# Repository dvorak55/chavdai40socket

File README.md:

# Chavdai40% Socket のご紹介

 - Chavdai40%は、ちゃぶだいよんじゅっぱーせんと、と読みます
 - 古き良きちゃぶ台をイメージしました

### ロゴ

### 基板写真

## ★★★　詳細な組み立て説明はキットに同梱の説明書に記載しておりますので省略しますが、この場所では写真が掲載可能なので、デコレーション例や、組み立てで難しそうな点をご紹介いたします　★★★

## Chavdai40% Socket（ソケット）の特徴
 - デコレーションできる、コンパクトで健気なキーボード
    - 40％キーボードというサイズ感（キー数44、または42）
    - ソケット対応なので、とりあえず組み立てて後でデコレーションするのも可能です
    - キーボードケースが付属しているので、持ち運びしやすいです
 - リーズナブルなキーキャップが選べます
    - Amazonでも売っているキーキャップが使えます
    - ちょっと高価なキーキャップも、もちろん使えます
    - 日本語キーボードの縦長Enterキーは使えません
 - Vial（ヴァイアル）というソフトに対応しています
    - 40％キーボードでも数字と記号が入力できます
    - Ctrl＋a等の組み合わせを1つのキーに登録することも可能です
 - USB-Cでパソコン／スマホ／タブレットと接続して使えます

## Chavdai40%の組み立て例
### 組立例１（Chavdai40% Socket ＋ ダイソー リメイクシート ナチュラルウッド ホワイト ＋ mtマスキングテープ ドットシリーズ（オレンジ、ピンク、青） ＋ mtマスキングテープ幅3ｍｍシリーズ ＋ ダイソー マスキングテープ ＋ ダイソー デコレーションシール ＋ 一般的な白地に黒文字のキーキャップ）
なるべくリーズナブルにおしゃれなデザインを目標に、ダイソーの白い木目のリメイクシートを下地に、パステル調のマスキングテープでデコレーションしてみました。キーキャップは同じくリーズナブルに入手できる白地に黒文字のキーキャップを取り付けて、シンプルながらも明るい印象に仕上げました。  

マスキングテープをランダムに配置して、おしゃれな感じにしてみました。  

リメイクシートとキーキャップセットは以下で購入可能です（2026年8月15日現在）  

●リメイクシート（ダイソー）  
[https://jp.daisonet.com/products/4900662759840)](https://jp.daisonet.com/products/4900662759840)  
●マスキングテープ（mtドット系）  
[https://shop.masking-tape.jp/products/list.php?category=99](https://shop.masking-tape.jp/products/list.php?category=99)  
●キーキャップ（Amazon.co.jp）  
[https://amzn.asia/d/0fVIauQW](https://amzn.asia/d/0fVIauQW)  

### 組立例２（Chavdai40% ＋ mtリメイクシートKapitza SUN ＋ Tai-Hao ABS Cubic Miami Surf）
※こちらはChavdai40％の以前のモデルでのデコレーション事例です。  
赤色の丸がかわいいリメイクシートと、ピンク色のキーキャップを組み合わせると、とってもポップな色合いになります。  

アクセントカラーの青色キーキャップが華を添えている感じですね。  

リメイクシートとキーキャップセットは現在は入手できません。  

### 組立例３（Chavdai40% ＋ mtリメイクシートKapitza FUJI ＋ GMK ECLIPSE）
※こちらはChavdai40％の以前のモデルでのデコレーション事例です。  
青色の三角がクールなリメイクシートと、青色黒色のキーキャップを組み合わせると、とっても引き締まった色合いになります。  

GMKのキーキャップセットなので、スペースキーを分割できます。この写真ではスペースキーが打ちやすいように上下逆につけています。  

リメイクシートとキーキャップセットは現在は入手できません。  

## デフォルトのキーマップ（JISの設定です）
### 44キーのキーマップ  
#### デフォルトレイヤー  

#### レイヤー1  

### 42キーのキーマップ
#### デフォルトレイヤー  

#### レイヤー1  

### 日本語キーボードか、英字キーボードかについて
Chavdai40% Socketでは、キットに付属の説明書内で、最初のキーマップは日本語キーボードのJISの設定にしています。  
もし英字キーボードの設定にしたい場合は、Vialの画面で以下の箇所を設定してください。  
上のメニューから『Keyboard Layout』を選び、その中から一番上にある『QWERTY』をクリックして選択します。  
これで、日本語キーボードのJISから、英字キーボードになります。  

## その他の問い合わせ先
X（twitter）: dombrick45 https://twitter.com/dombrick45  
※キットに同梱の説明書にメールアドレスが記載されております。

## 難しそうなポイント
### １．スタビライザーの取り付け
スタビライザーは、説明書にあるように大きな方の穴に爪を引っ掛けた後、小さい方の穴にもう片方の爪を嵌める手順で取り付けます。  
このスタビライザーを取り付けた後、キースイッチ・キーキャップを付けると、キースイッチがうまく戻らないことがあります。  
その場合は、キーキャップをつまんで、上下左右に動かしてみて下さい。 　
少し遊びができると、キースイッチがうまく戻るようになります。  
### ２．デコレーションの後に、キースイッチ・スタビライザーを取り付ける
おもて面にデコレーションのシール・シートを貼ると、キースイッチ・スタビライザーを取り付ける時、少しキツくなります。  
簡単にするため、キースイッチ・スタビライザーの取り付け箇所のシール・シートに、あらかじめ鉛筆やボールペンで穴を空けておくと良いです。
また、デコレーションを3枚ほど重ねた箇所のスイッチ取り付けはかなり辛いので、その場合は、スイッチの穴の箇所だけデコレーションを破いて取り除くと良いです。

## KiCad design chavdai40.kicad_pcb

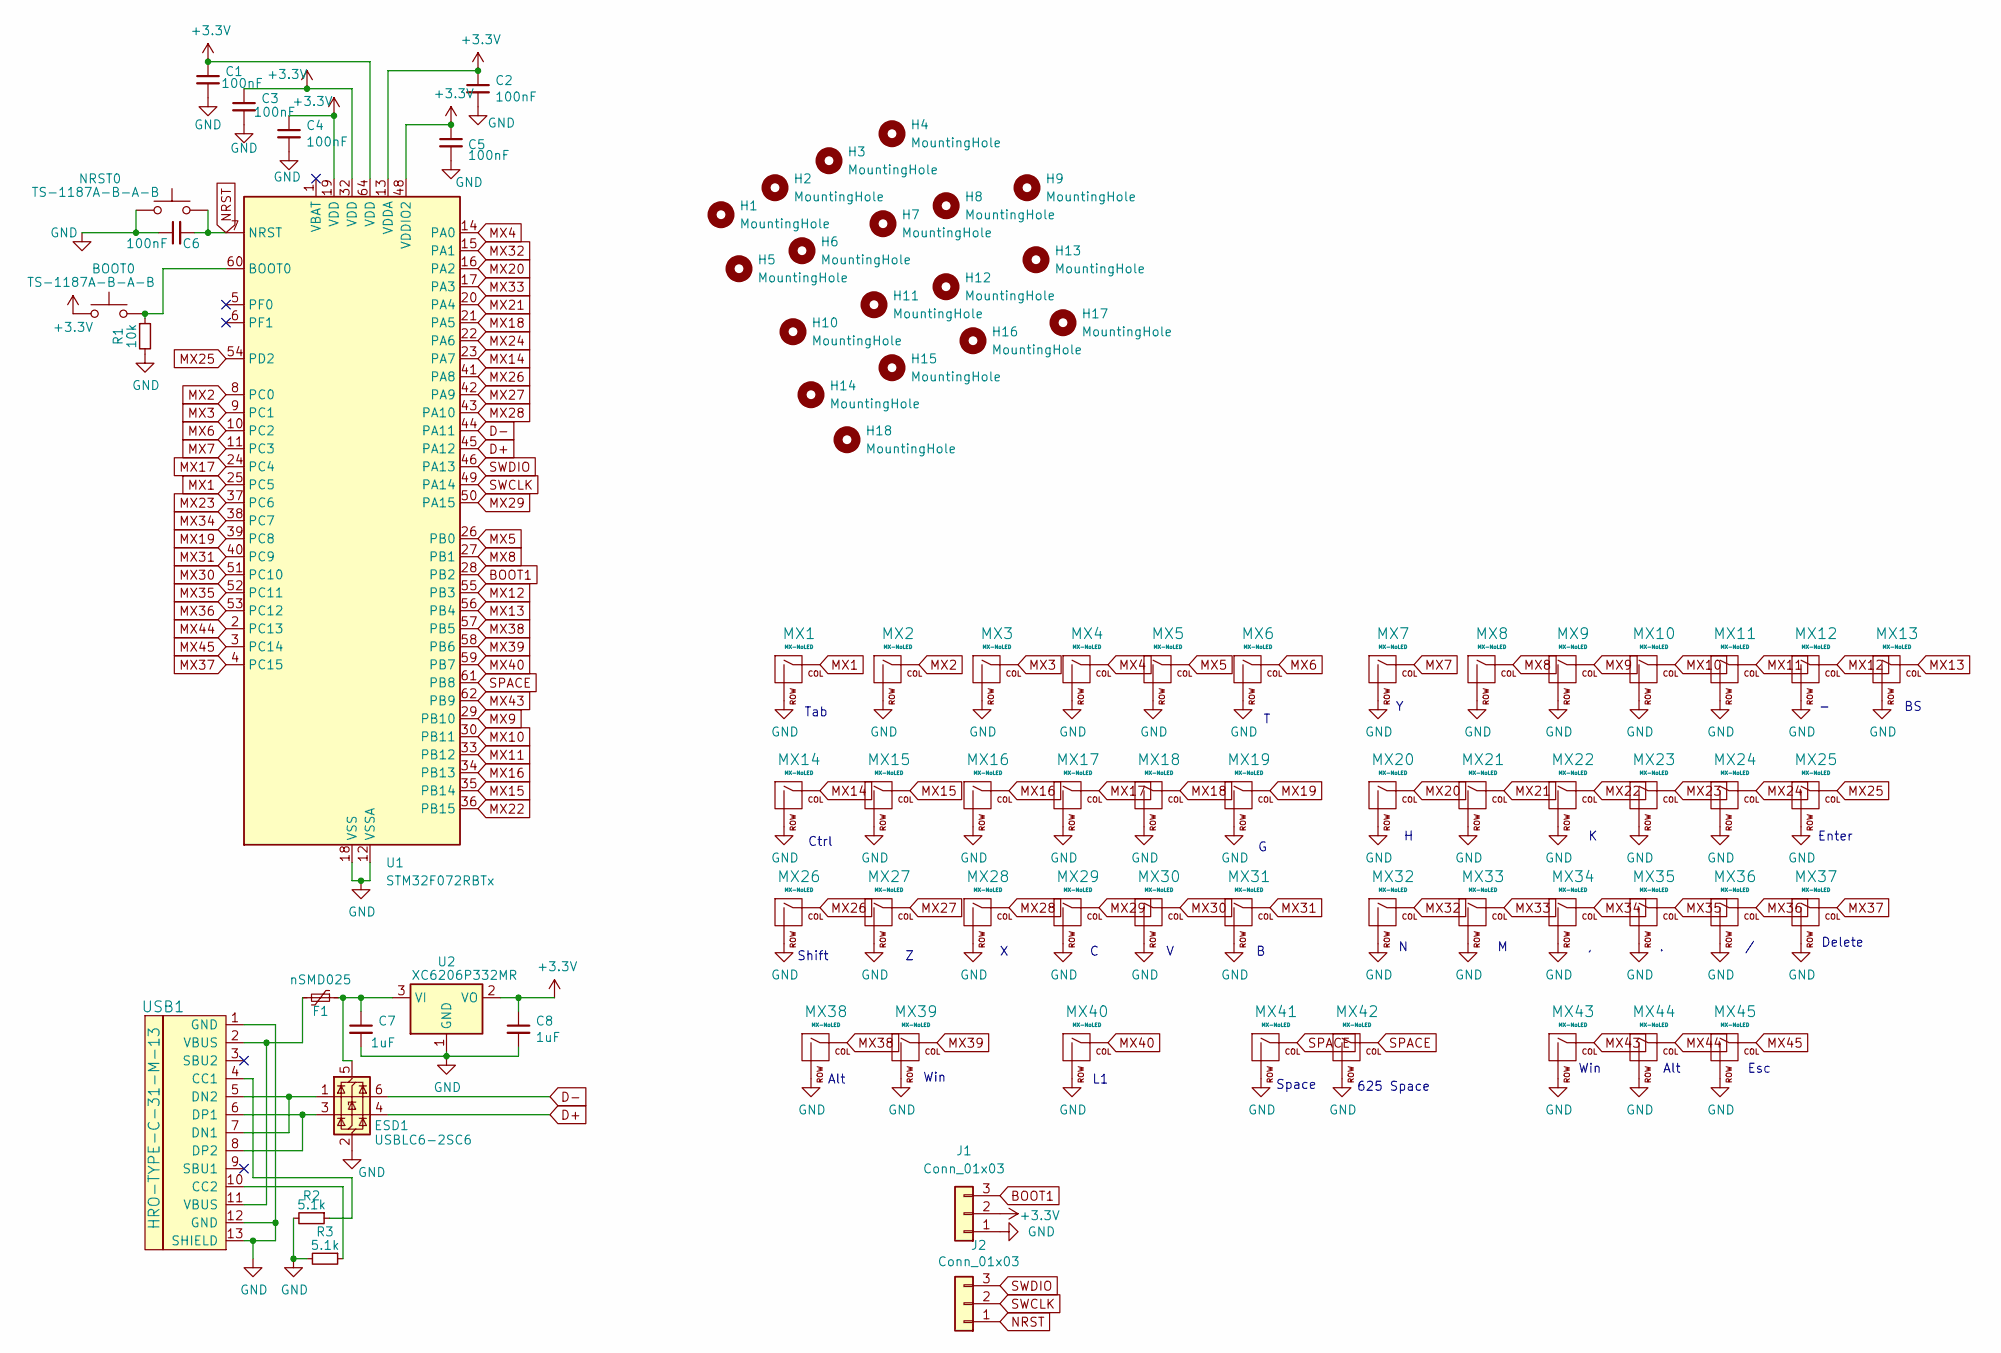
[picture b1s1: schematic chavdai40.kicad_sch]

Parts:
BOOT0: TS-1187A-B-A-B; SKQGADE010
C1, C2, C3, C4, C5, C6: 100nF; C_0402_1005Metric
C7, C8: 1uF; C_0603_1608Metric
ESD1: USBLC6-2SC6; SOT-23-6
F1: nSMD025; Fuse_1206_3216Metric
H1, H2, H11, H12, H13, H14, H15, H16, H17, H18: MountingHole; TestPoint_Pad_D4.0mm
H3, H4, H5, H6, H7, H8, H9, H10: MountingHole; TestPoint_THTPad_D4.0mm_Drill2.0mm
J1, J2: Conn_01x03; PinHeader_1x03_P2.54mm_Vertical
MX1, MX13: MX-NoLED; MXOnly-1.5U-Hotswap
MX2, MX3, MX4, MX5, MX6, MX7, MX8, MX9, MX10, MX11, MX12, MX15, MX16, MX17, MX18, MX19, MX20, MX21, MX22, MX23, MX24, MX27, MX28, MX29, MX30, MX31, MX32, MX33, MX34, MX35: MX-NoLED; MXOnly-1U-Hotswap
MX14: MX-NoLED; MXOnly-1.75U-Hotswap
MX25, MX26, MX40: MX-NoLED; MXOnly-2.25U-Hotswap-ReversedStabilizers
MX36, MX37, MX38, MX39, MX43, MX44, MX45: MX-NoLED; MXOnly-1.25U-Hotswap
MX41: MX-NoLED; MXOnly-2.75U-Hotswap-ReversedStabilizers
MX42: MX-NoLED; MXOnly-6.25U-Hotswap-ReversedStabilizers
NRST0: TS-1187A-B-A-B; SKQGADE010
R1: 10k; R_0603_1608Metric
R2, R3: 5.1k; R_0603_1608Metric
U1: STM32F072RBTx; LQFP-64_10x10mm_P0.5mm
U2: XC6206P332MR; TSOT-23
USB1: HRO-TYPE-C-31-M-13

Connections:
+3.3V: BOOT0.1, C1.1, C2.1, C3.1, C4.1, C5.1, C8.1, J1.2, U1.13 (VDDA), U1.19 (VDD), U1.32 (VDD), U1.48 (VDDIO2), U1.64 (VDD), U2.2 (VO)
BOOT1: J1.3, U1.28 (PB2)
D+: ESD1.4 (I/O2), U1.45 (PA12)
D-: ESD1.6 (I/O1), U1.44 (PA11)
GND: C1.2, C2.2, C3.2, C4.2, C5.2, C6.1, C7.2, C8.2, ESD1.2 (GND), J1.1, MX1.2 (ROW), MX2.2 (ROW), MX3.2 (ROW), MX4.2 (ROW), MX5.2 (ROW), MX6.2 (ROW), MX7.2 (ROW), MX8.2 (ROW), MX9.2 (ROW), MX10.2 (ROW), MX11.2 (ROW), MX12.2 (ROW), MX13.2 (ROW), MX14.2 (ROW), MX15.2 (ROW), MX16.2 (ROW), MX17.2 (ROW), MX18.2 (ROW), MX19.2 (ROW), MX20.2 (ROW), MX21.2 (ROW), MX22.2 (ROW), MX23.2 (ROW), MX24.2 (ROW), MX25.2 (ROW), MX26.2 (ROW), MX27.2 (ROW), MX28.2 (ROW), MX29.2 (ROW), MX30.2 (ROW), MX31.2 (ROW), MX32.2 (ROW), MX33.2 (ROW), MX34.2 (ROW), MX35.2 (ROW), MX36.2 (ROW), MX37.2 (ROW), MX38.2 (ROW), MX39.2 (ROW), MX40.2 (ROW), MX41.2 (ROW), MX42.2 (ROW), MX43.2 (ROW), MX44.2 (ROW), MX45.2 (ROW), NRST0.1, R1.2, R2.2, R3.2, U1.12 (VSSA), U1.18 (VSS), U1.31 (VSS), U1.47 (VSS), U1.63 (VSS), U2.1 (GND), USB1.1 (GND), USB1.12 (GND), USB1.13 (SHIELD)
MX1: MX1.1 (COL), U1.25 (PC5)
MX2: MX2.1 (COL), U1.8 (PC0)
MX3: MX3.1 (COL), U1.9 (PC1)
MX4: MX4.1 (COL), U1.14 (PA0)
MX5: MX5.1 (COL), U1.26 (PB0)
MX6: MX6.1 (COL), U1.10 (PC2)
MX7: MX7.1 (COL), U1.11 (PC3)
MX8: MX8.1 (COL), U1.27 (PB1)
MX9: MX9.1 (COL), U1.29 (PB10)
MX10: MX10.1 (COL), U1.30 (PB11)
MX11: MX11.1 (COL), U1.33 (PB12)
MX12: MX12.1 (COL), U1.55 (PB3)
MX13: MX13.1 (COL), U1.56 (PB4)
MX14: MX14.1 (COL), U1.23 (PA7)
MX15: MX15.1 (COL), U1.35 (PB14)
MX16: MX16.1 (COL), U1.34 (PB13)
MX17: MX17.1 (COL), U1.24 (PC4)
MX18: MX18.1 (COL), U1.21 (PA5)
MX19: MX19.1 (COL), U1.39 (PC8)
MX20: MX20.1 (COL), U1.16 (PA2)
MX21: MX21.1 (COL), U1.20 (PA4)
MX22: MX22.1 (COL), U1.36 (PB15)
MX23: MX23.1 (COL), U1.37 (PC6)
MX24: MX24.1 (COL), U1.22 (PA6)
MX25: MX25.1 (COL), U1.54 (PD2)
MX26: MX26.1 (COL), U1.41 (PA8)
MX27: MX27.1 (COL), U1.42 (PA9)
MX28: MX28.1 (COL), U1.43 (PA10)
MX29: MX29.1 (COL), U1.50 (PA15)
MX30: MX30.1 (COL), U1.51 (PC10)
MX31: MX31.1 (COL), U1.40 (PC9)
MX32: MX32.1 (COL), U1.15 (PA1)
MX33: MX33.1 (COL), U1.17 (PA3)
MX34: MX34.1 (COL), U1.38 (PC7)
MX35: MX35.1 (COL), U1.52 (PC11)
MX36: MX36.1 (COL), U1.53 (PC12)
MX37: MX37.1 (COL), U1.4 (PC15)
MX38: MX38.1 (COL), U1.57 (PB5)
MX39: MX39.1 (COL), U1.58 (PB6)
MX40: MX40.1 (COL), U1.59 (PB7)
MX43: MX43.1 (COL), U1.62 (PB9)
MX44: MX44.1 (COL), U1.2 (PC13)
MX45: MX45.1 (COL), U1.3 (PC14)
NRST: C6.2, J2.1, NRST0.2, U1.7 (NRST)
unnamed: C7.1, ESD1.5 (VBUS), F1.1, U2.3 (VI)
unnamed: F1.2, USB1.2 (VBUS), USB1.11 (VBUS)
unnamed: BOOT0.2, R1.1, U1.60 (BOOT0)
unnamed: R2.1, USB1.4 (CC1)
unnamed: R3.1, USB1.10 (CC2)
unnamed: ESD1.1 (I/O1), USB1.5 (DN2), USB1.7 (DN1)
unnamed: ESD1.3 (I/O2), USB1.6 (DP1), USB1.8 (DP2)
SPACE: MX41.1 (COL), MX42.1 (COL), U1.61 (PB8)
SWCLK: J2.2, U1.49 (PA14)
SWDIO: J2.3, U1.46 (PA13)

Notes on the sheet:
Win
Space
Enter
Delete
Esc
625 Space
Tab
Alt
Ctrl
Shift

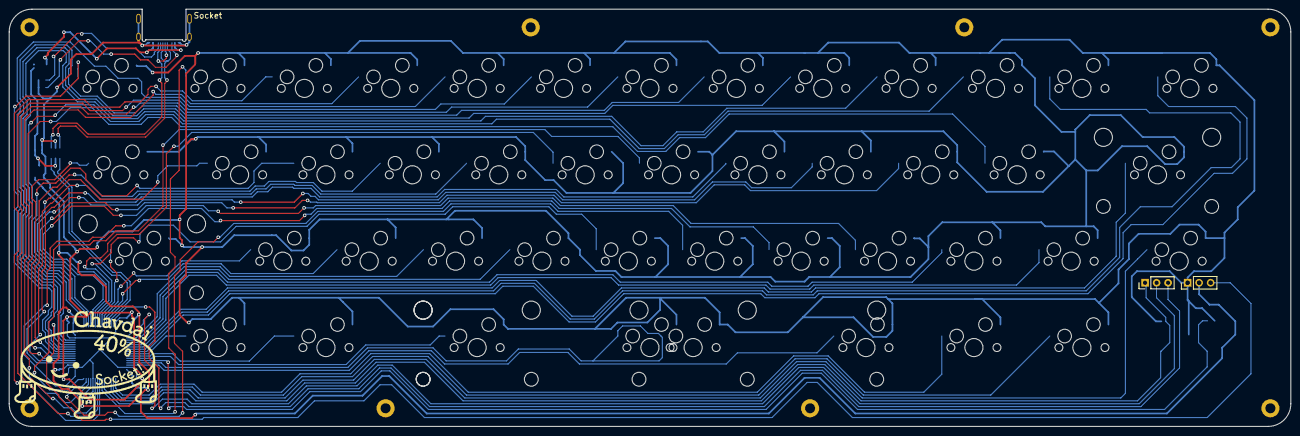
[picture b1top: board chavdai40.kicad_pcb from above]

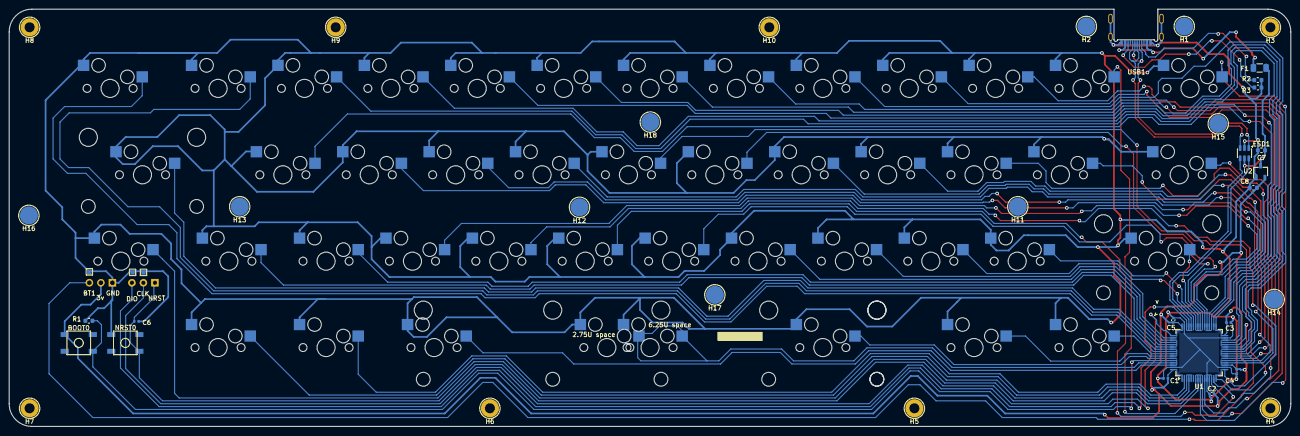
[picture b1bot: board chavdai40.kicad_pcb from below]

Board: 2 copper layers, 282.6 x 92.0 mm, 83 parts (36 on the bottom side), 59 nets.
